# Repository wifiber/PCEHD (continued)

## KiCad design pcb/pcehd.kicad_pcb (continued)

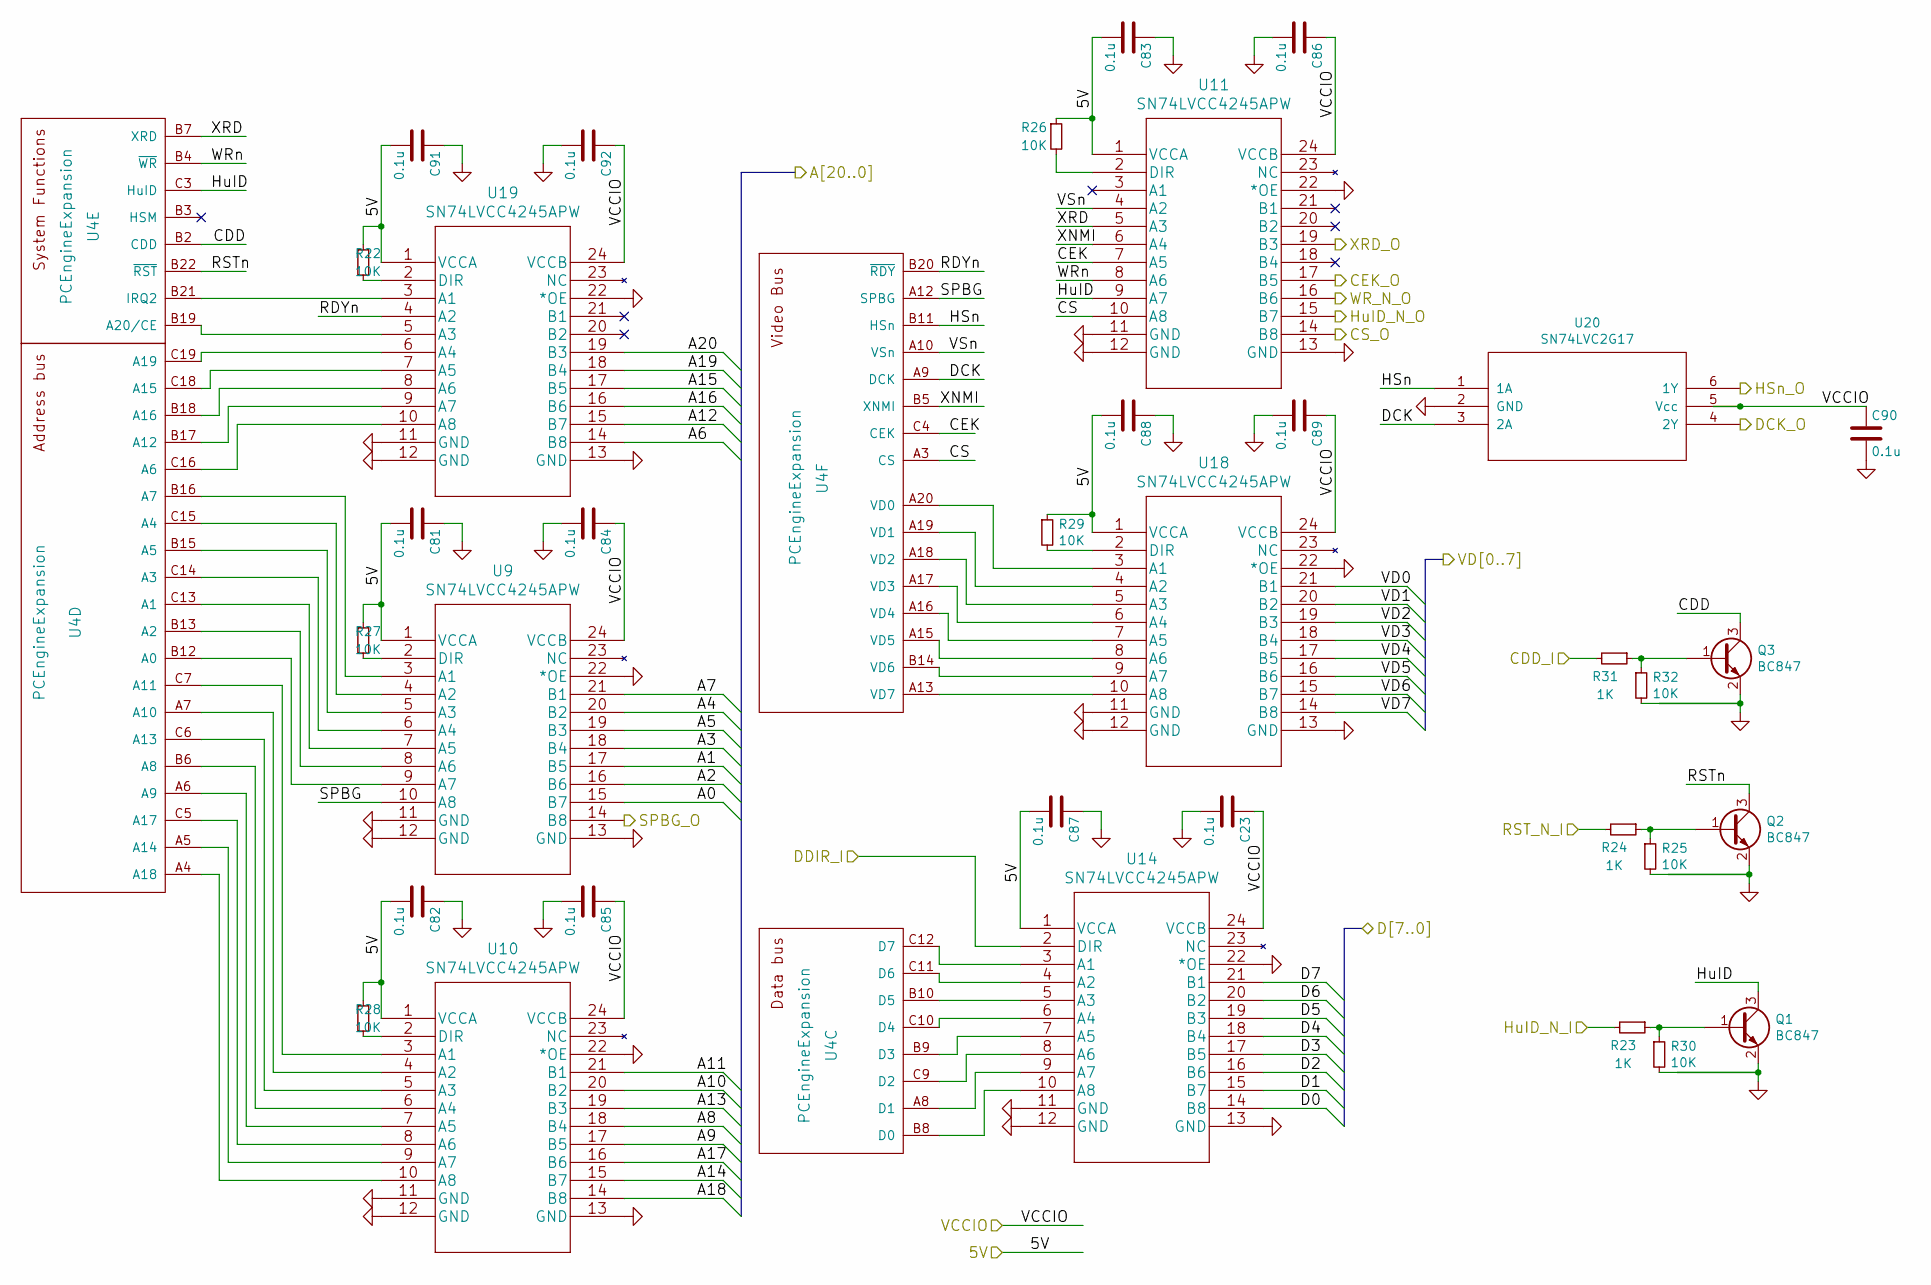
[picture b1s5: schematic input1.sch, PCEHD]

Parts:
C23, C81, C82, C83, C84, C85, C86, C87, C88, C89, C90, C91, C92: 0.1u; SM0603_Capa_libcms
Q1, Q2, Q3: BC847; SOT-23
R22, R25, R26, R27, R28, R29, R30, R32: 10K; SM0603_Resistor_libcms
R23, R24, R31: 1K; SM0603_Resistor_libcms
U4: PCEngineExpansion
U9, U10, U11, U14, U18, U19: SN74LVCC4245APW
U20: SN74LVC2G17; SOT-23-6_Handsoldering

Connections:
/5V: C81.2, C82.2, C83.2, C87.2, C88.2, C91.2, R22.1, R26.1, R27.1, R28.1, R29.1, U9.1 (VCCA), U10.1 (VCCA), U11.1 (VCCA), U14.1 (VCCA), U18.1 (VCCA), U19.1 (VCCA); also elsewhere on the board
/fpga1/A0: U9.15 (B7); also elsewhere on the board
/fpga1/A1: U9.17 (B5); also elsewhere on the board
/fpga1/A2: U9.16 (B6); also elsewhere on the board
/fpga1/A3: U9.18 (B4); also elsewhere on the board
/fpga1/A4: U9.20 (B2); also elsewhere on the board
/fpga1/A5: U9.19 (B3); also elsewhere on the board
/fpga1/A6: U19.14 (B8); also elsewhere on the board
/fpga1/A7: U9.21 (B1); also elsewhere on the board
/fpga1/A8: U10.18 (B4); also elsewhere on the board
/fpga1/A9: U10.17 (B5); also elsewhere on the board
/fpga1/A10: U10.20 (B2); also elsewhere on the board
/fpga1/A11: U10.21 (B1); also elsewhere on the board
/fpga1/A12: U19.15 (B7); also elsewhere on the board
/fpga1/A13: U10.19 (B3); also elsewhere on the board
/fpga1/A14: U10.15 (B7); also elsewhere on the board
/fpga1/A15: U19.17 (B5); also elsewhere on the board
/fpga1/A16: U19.16 (B6); also elsewhere on the board
/fpga1/A17: U10.16 (B6); also elsewhere on the board
/fpga1/A18: U10.14 (B8); also elsewhere on the board
/fpga1/A19: U19.18 (B4); also elsewhere on the board
/fpga1/A20: U19.19 (B3); also elsewhere on the board
/fpga1/CEK: U11.17 (B5); also elsewhere on the board
/fpga1/CS: U11.14 (B8); also elsewhere on the board
/fpga1/D0: U14.14 (B8); also elsewhere on the board
/fpga1/D1: U14.15 (B7); also elsewhere on the board
/fpga1/D2: U14.16 (B6); also elsewhere on the board
/fpga1/D3: U14.17 (B5); also elsewhere on the board
/fpga1/D4: U14.18 (B4); also elsewhere on the board
/fpga1/D5: U14.19 (B3); also elsewhere on the board
/fpga1/D6: U14.20 (B2); also elsewhere on the board
/fpga1/D7: U14.21 (B1); also elsewhere on the board
/fpga1/DCK: U20.4 (2Y); also elsewhere on the board
/fpga1/DDIR: U14.2 (DIR); also elsewhere on the board
/fpga1/HuID_N: U11.15 (B7); also elsewhere on the board
/fpga1/SPBG: U9.14 (B8); also elsewhere on the board
/fpga1/VD0: U18.21 (B1); also elsewhere on the board
/fpga1/VD1: U18.20 (B2); also elsewhere on the board
/fpga1/VD2: U18.19 (B3); also elsewhere on the board
/fpga1/VD3: U18.18 (B4); also elsewhere on the board
/fpga1/VD4: U18.17 (B5); also elsewhere on the board
/fpga1/VD5: U18.16 (B6); also elsewhere on the board
/fpga1/VD6: U18.15 (B7); also elsewhere on the board
/fpga1/VD7: U18.14 (B8); also elsewhere on the board
/fpga1/WR_N: U11.16 (B6); also elsewhere on the board
/fpga1/XRD: U11.19 (B3); also elsewhere on the board
/input1/CDD: Q3.3 (C), U4.B2 (CDD)
/input1/CDD_I: R31.2; also elsewhere on the board
/input1/CEK: U4.C4 (CEK), U11.7 (A5)
/input1/CS: U4.A3 (CS), U11.10 (A8)
/input1/DCK: U4.A9 (DCK), U20.3 (2A)
/input1/HSn: U4.B11 (HSn), U20.1 (1A)
/input1/HSn_O: U20.6 (1Y); also elsewhere on the board
/input1/HuID: Q1.3 (C), U4.C3 (HuID), U11.9 (A7)
/input1/HuID_N_I: R23.2; also elsewhere on the board
/input1/RDYn: U4.B20 (~RDY), U19.4 (A2)
/input1/RST_N_I: R24.2; also elsewhere on the board
/input1/RSTn: Q2.3 (C), U4.B22 (~RST)
/input1/SPBG: U4.A12 (SPBG), U9.10 (A8)
/input1/VSn: U4.A10 (VSn), U11.4 (A2)
/input1/WRn: U4.B4 (~WR), U11.8 (A6)
/input1/XNMI: U4.B5 (XNMI), U11.6 (A4)
/input1/XRD: U4.B7 (XRD), U11.5 (A3)
GND: C23.2, C81.1, C82.1, C83.1, C84.2, C85.2, C86.2, C87.1, C88.1, C89.2, C90.2, C91.1, C92.2, Q1.2 (E), Q2.2 (E), Q3.2 (E), R25.2, R30.2, R32.2, U9.11 (GND), U9.12 (GND), U9.13 (GND), U9.22 (*OE), U10.11 (GND), U10.12 (GND), U10.13 (GND), U10.22 (*OE), U11.11 (GND), U11.12 (GND), U11.13 (GND), U11.22 (*OE), U14.11 (GND), U14.12 (GND), U14.13 (GND), U14.22 (*OE), U18.11 (GND), U18.12 (GND), U18.13 (GND), U18.22 (*OE), U19.11 (GND), U19.12 (GND), U19.13 (GND), U19.22 (*OE), U20.2 (GND); also elsewhere on the board
unnamed: Q1.1 (B), R23.1, R30.1
unnamed: Q2.1 (B), R24.1, R25.1
unnamed: Q3.1 (B), R31.1, R32.1
unnamed: R22.2, U19.2 (DIR)
unnamed: R26.2, U11.2 (DIR)
unnamed: R27.2, U9.2 (DIR)
unnamed: R28.2, U10.2 (DIR)
unnamed: R29.2, U18.2 (DIR)
unnamed: U4.B12 (A0), U9.9 (A7)
unnamed: U4.B13 (A2), U9.8 (A6)
unnamed: U4.B15 (A5), U9.5 (A3)
unnamed: U4.B16 (A7), U9.3 (A1)
unnamed: U4.C13 (A1), U9.7 (A5)
unnamed: U4.C14 (A3), U9.6 (A4)
unnamed: U4.C15 (A4), U9.4 (A2)
unnamed: U4.C7 (A11), U10.3 (A1)
unnamed: U4.A7 (A10), U10.4 (A2)
unnamed: U4.C6 (A13), U10.5 (A3)
unnamed: U4.B6 (A8), U10.6 (A4)
unnamed: U4.A6 (A9), U10.7 (A5)
unnamed: U4.C5 (A17), U10.8 (A6)
unnamed: U4.A5 (A14), U10.9 (A7)
unnamed: U4.A4 (A18), U10.10 (A8)
unnamed: U4.C12 (D7), U14.3 (A1)
unnamed: U4.C11 (D6), U14.4 (A2)
unnamed: U4.B10 (D5), U14.5 (A3)
unnamed: U4.C10 (D4), U14.6 (A4)
unnamed: U4.B9 (D3), U14.7 (A5)
unnamed: U4.C9 (D2), U14.8 (A6)
unnamed: U4.A8 (D1), U14.9 (A7)
unnamed: U4.B8 (D0), U14.10 (A8)
unnamed: U4.A20 (VD0), U18.3 (A1)
unnamed: U4.A19 (VD1), U18.4 (A2)
unnamed: U4.A18 (VD2), U18.5 (A3)
unnamed: U4.A17 (VD3), U18.6 (A4)
unnamed: U4.A16 (VD4), U18.7 (A5)
unnamed: U4.A15 (VD5), U18.8 (A6)
unnamed: U4.B14 (VD6), U18.9 (A7)
unnamed: U4.A13 (VD7), U18.10 (A8)
unnamed: U4.B21 (IRQ2), U19.3 (A1)
unnamed: U4.B19 (A20/CE), U19.5 (A3)
unnamed: U4.C19 (A19), U19.6 (A4)
unnamed: U4.C18 (A15), U19.7 (A5)
unnamed: U4.B18 (A16), U19.8 (A6)
unnamed: U4.B17 (A12), U19.9 (A7)
unnamed: U4.C16 (A6), U19.10 (A8)
VCC: C23.1, C84.1, C85.1, C86.1, C89.1, C90.1, C92.1, U9.24 (VCCB), U10.24 (VCCB), U11.24 (VCCB), U14.24 (VCCB), U18.24 (VCCB), U19.24 (VCCB), U20.5 (Vcc); also elsewhere on the board

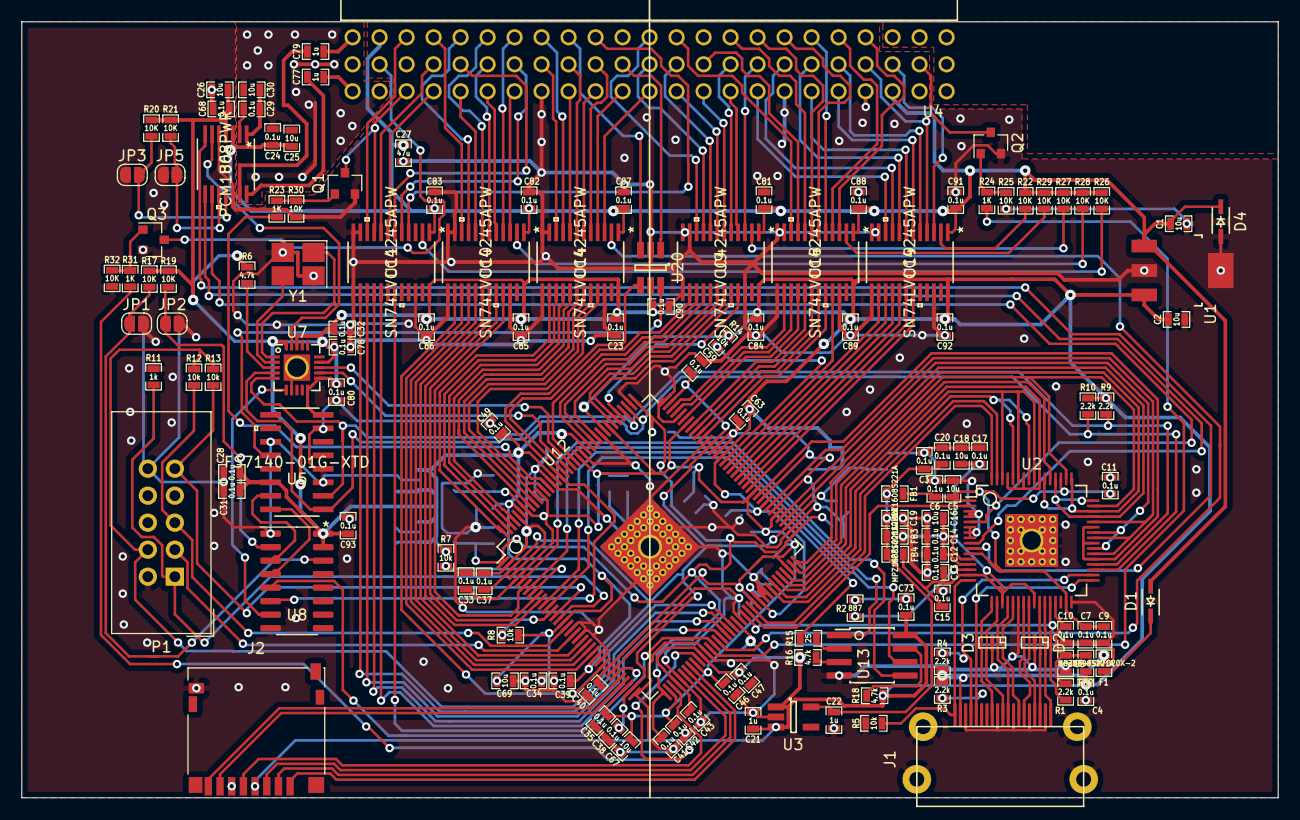
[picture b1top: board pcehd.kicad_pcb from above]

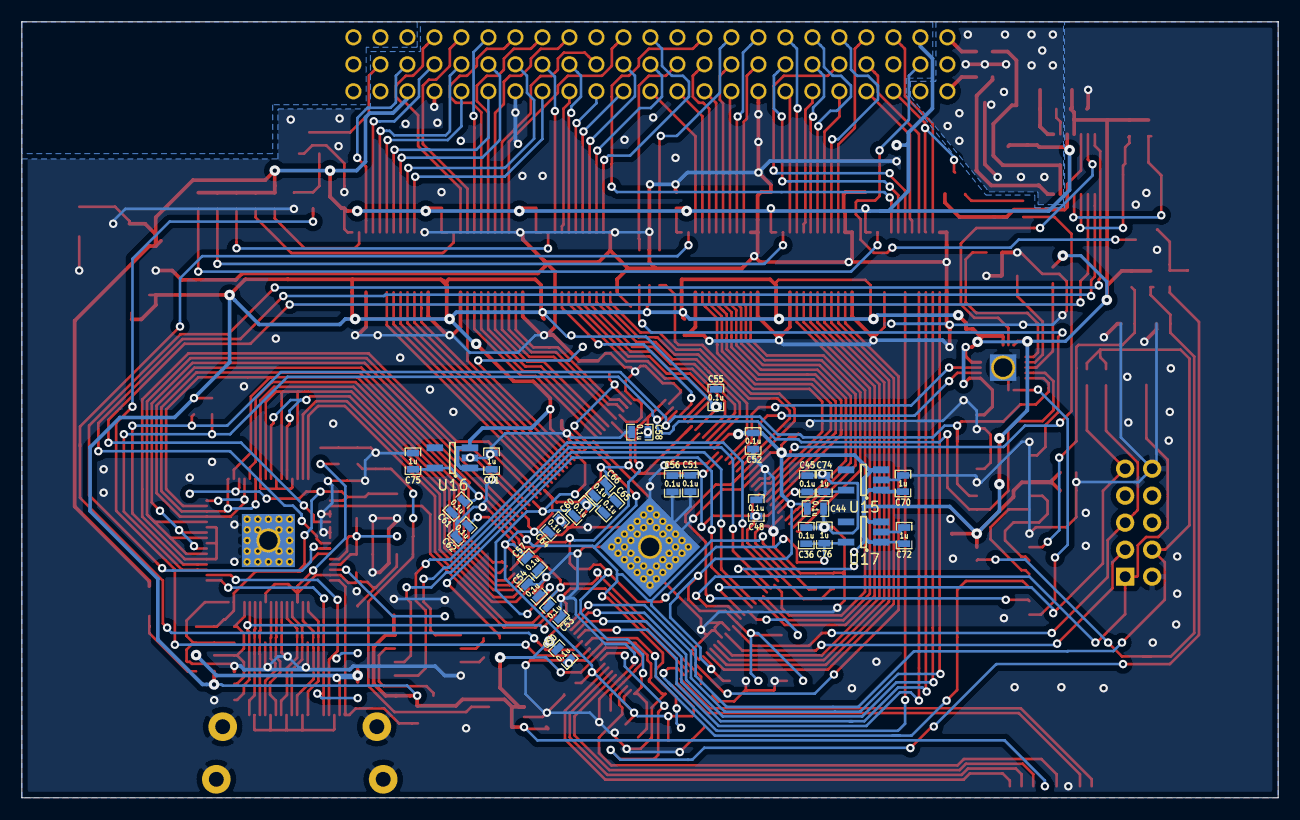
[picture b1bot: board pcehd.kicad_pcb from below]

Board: 2 copper layers, 118.2 x 73.0 mm, 165 parts (28 on the bottom side), 192 nets.

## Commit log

2020-01-04 Finished initial schematic with audio
2020-01-04 Added power unit from expansion connector symbol
2020-01-07 Cleaned up schematic, moved connections to busses
2020-01-08 Added clock selection
2020-01-13 Added FS7140 PLL, moved to level-shift '245
2020-01-13 Assigned footprints, begin layout
2020-01-13 Expansion connection re-order for layout
2020-01-14 Begin layout
2020-01-14 Layout checkpoint
2020-01-14 Layout check-in
2020-01-15 New layout
2020-01-15 New layout checkpoint
2020-01-16 Removed unneeded jumpers
2020-01-17 Layout near complete
2020-01-17 Layout almost done
2020-01-17 100% parts placed, 95% routed
2020-01-18 Removed bypass components and routed all power
2020-01-18 Finished place and route
2020-01-19 Added CDD signal to last open IO pin
2020-01-20 Finished version 0.1
